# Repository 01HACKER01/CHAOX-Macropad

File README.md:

# CHAOX-Macropad
A macro-pad with 16 keys and a rotary encoder powered by Seeed XIAO RP2040

I wanted something that was actually useful on my desk, but also something I could completely customize so i made this from the PCB and firmware to the case.

## Things present in the chaox-pad

- 16 MX-style mechanical switches
- 1 EC11 rotary encoders
- Seeed XIAO RP2040
- 1N4148 diodes
- Custom PCB
- Custom 3D-printed case
- CHAOX engraved top plate

## The design

I designed this case in FreeCAD.

I kept the top plate removable, so the switches and electronics can be assembled more easily.

## PCB

I used Kicad 10 to make my PCB

The PCB files are in:

`PCB/`

## Firmware

The firmware is written using KMK and CircuitPython.

It currently includes:

- Multiple layers
- Keyboard shortcuts
- Text macros
- Numpad layer
- Rotary encoder controls
- Volume controls
- Tab switching
- Media controls

Firmware files are in:

`Firmware/`

## CAD files

All of the case files are available in:

`CAD/`

You can open the FreeCAD file if you want to modify the design yourself.

The STEP files are also included for anyone who wants to work with the case in another CAD program.

## BOM

- Seeed XIAO RP2040 -1
- Through-hole 1N4148 Diodes -16
- MX-Style switches -16
- EC11 Rotary encoders -1
- M3x16mm screws -4
- M3x5mx4mm headset inserts -4
- M2x3mm screw -1

## Why I made it

I wanted to build something but didn't know what to build so then i saw a reel of alex saying i made this hackpad and u can build it too so i got inspired and made this.

There will probably be things I change in the future, but this is the current version of the Chaox-Macropad
---

Made by **01HACKER01** 🖤

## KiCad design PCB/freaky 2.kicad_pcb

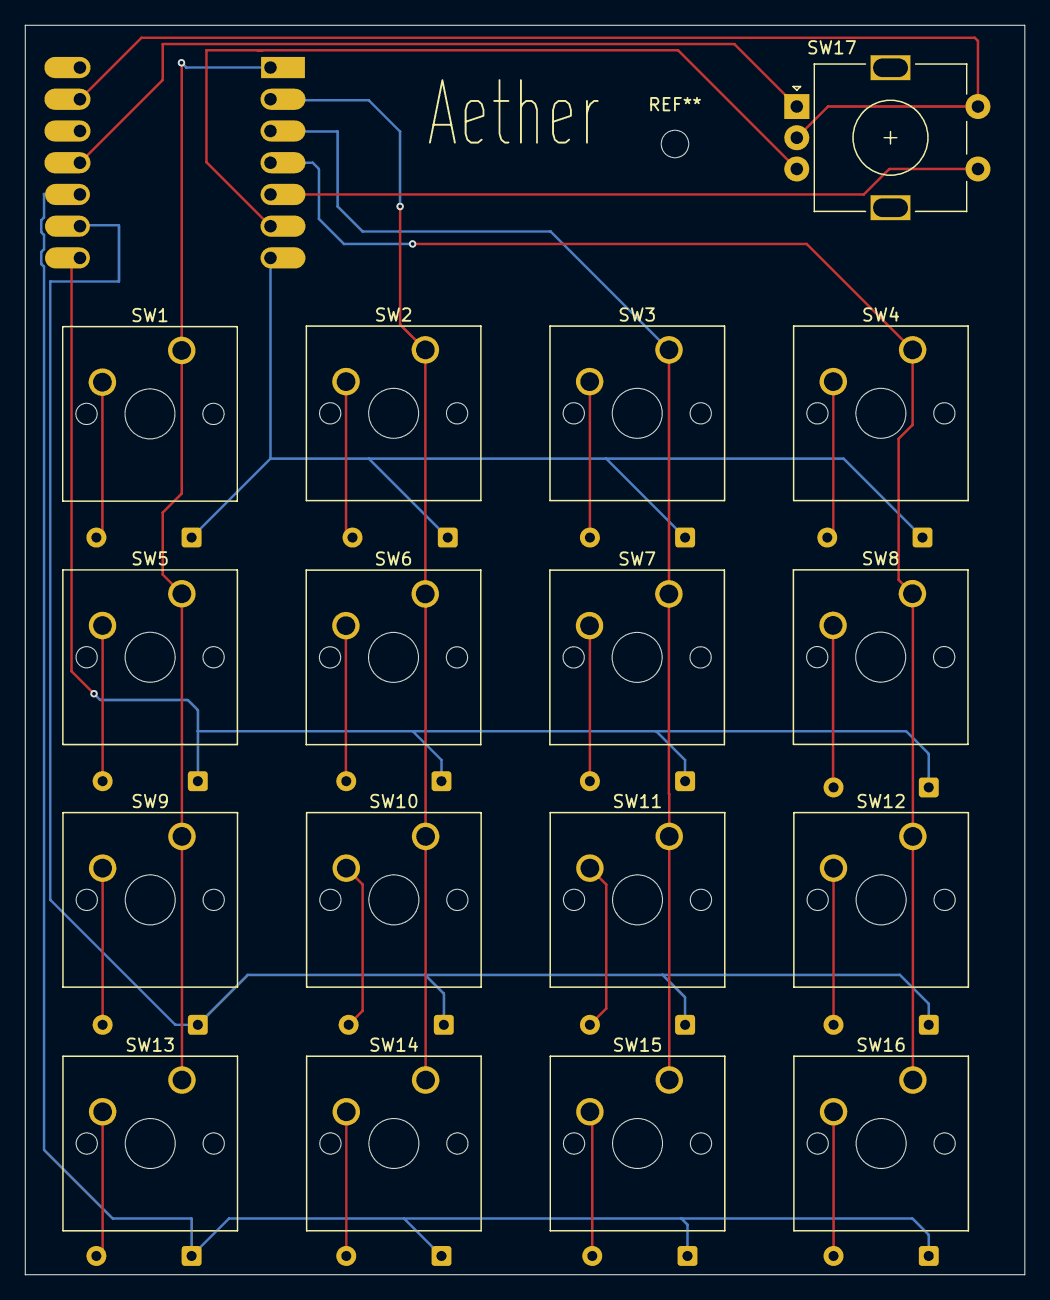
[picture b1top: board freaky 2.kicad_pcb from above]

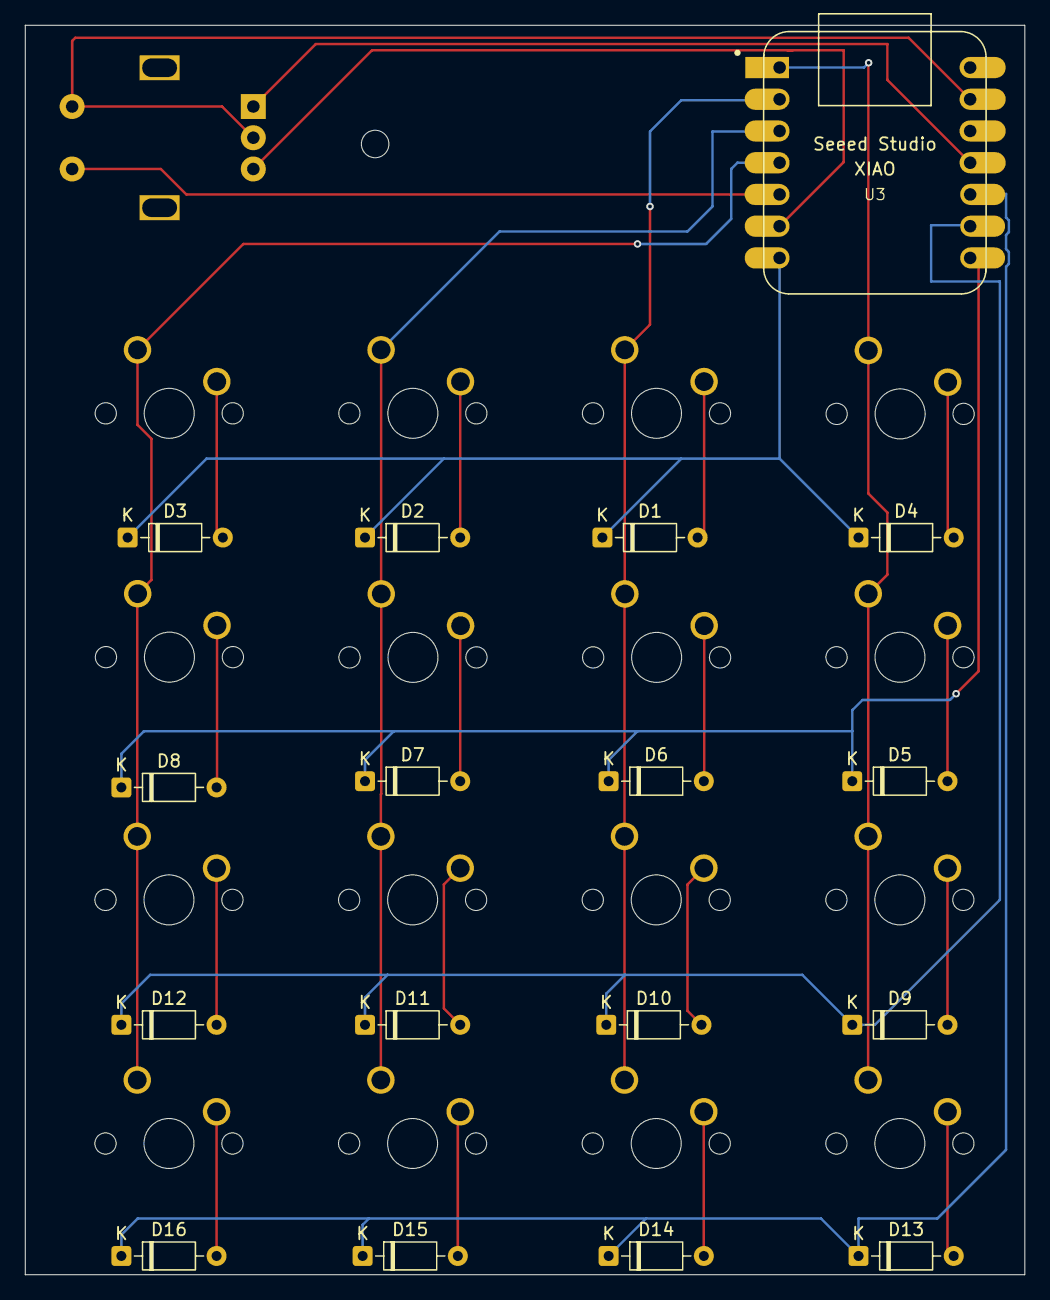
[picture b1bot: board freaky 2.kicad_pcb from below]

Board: 2 copper layers, 80.0 x 100.0 mm, 34 parts (17 on the bottom side), 28 nets.

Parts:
D1, D2, D3, D4, D5, D6, D7, D8, D9, D10, D11, D12, D13, D14, D15, D16: 1N4148; D_DO-35_SOD27_P7.62mm_Horizontal
SW1, SW2, SW3, SW4, SW5, SW6, SW7, SW8, SW9, SW10, SW11, SW12, SW13, SW14, SW15, SW16: SW_Push; SW_Cherry_MX_1.00u_PCB
SW17: RotaryEncoder_Switch; RotaryEncoder_Alps_EC11E-Switch_Vertical_H20mm
U3: MOUDLE-SEEEDUINO-XIAO; XIAO-Generic-Hybrid-14P-2.54-21X17.8MM

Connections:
unnamed: D1.2 (A), SW2.2
unnamed: D1.1 (K), D2.1 (K), D3.1 (K), D4.1 (K), U3.7 (PB08_A6_D6_TX)
unnamed: D2.2 (A), SW3.2
unnamed: D3.2 (A), SW4.2
unnamed: D4.2 (A), SW1.2
unnamed: D5.2 (A), SW5.2
unnamed: D5.1 (K), D6.1 (K), D7.1 (K), D8.1 (K), U3.8 (PB09_A7_D7_RX)
unnamed: D6.2 (A), SW6.2
unnamed: D7.2 (A), SW7.2
unnamed: D8.2 (A), SW8.2
unnamed: D9.2 (A), SW9.2
unnamed: D10.2 (A), SW10.2
unnamed: D9.1 (K), D10.1 (K), D11.1 (K), D12.1 (K), U3.9 (PA7_A8_D8_SCK)
unnamed: D11.2 (A), SW11.2
unnamed: D12.2 (A), SW12.2
unnamed: D13.2 (A), SW13.2
unnamed: D13.1 (K), D14.1 (K), D15.1 (K), D16.1 (K), U3.10 (PA5_A9_D9_MISO)
unnamed: D14.2 (A), SW14.2
unnamed: D15.2 (A), SW15.2
unnamed: D16.2 (A), SW16.2
unnamed: SW17.C, SW17.S2, U3.13 (GND)
unnamed: SW1.1, SW5.1, SW9.1, SW13.1, U3.1 (PA02_A0_D0)
unnamed: SW2.1, SW6.1, SW10.1, SW14.1, U3.2 (PA4_A1_D1)
unnamed: SW17.A, U3.11 (PA6_A10_D10_MOSI)
unnamed: SW17.S1, U3.5 (PA8_A4_D4_SDA)
unnamed: SW17.B, U3.6 (PA9_A5_D5_SCL)
unnamed: SW3.1, SW7.1, SW11.1, SW15.1, U3.3 (PA10_A2_D2)
unnamed: SW4.1, SW8.1, SW12.1, SW16.1, U3.4 (PA11_A3_D3)
